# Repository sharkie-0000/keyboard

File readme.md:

# Custom Mechanical Keyboard

My first go at designing and building a custom mechanical keyboard!

This is a custom 60% mechanical keyboard built around a PCB designed in KiCad. This keyboard contains 61 mechanical switches, a Raspberry Pi Pico microcontroller, rotary encoder and small OLED screen.

The aim of this project was to learn how keyboards work internally. I wanted to design a keyboard from scratch including the electrical circuit, switch matrix, PCB design and layout, firmware and case design.

## What is this?

Custom 60% mechanical keyboard with a 61-key layout and custom PCB

Features a 5 row x 14 column switch matrix with individual diodes on each switch to reduce the chance of accidental keystrokes when multiple keys are pressed.

Includes:
Raspberry Pi Pico (RP2040) main controller
61 mechanical switches
61 matrix diodes
Rotary encoder with push button
0.96 inch OLED screen
Custom PCB and 3D designed case components

## Why build this?

This was my first mechanical keyboard project and I wanted to push myself a bit.

I’ve always had an interest in understanding electronics, therefore building a mechanical keyboard was a great opportunity to get hands on with electronics, PCB design, CAD and programming.

I wanted to learn:
How to create a circuit schematic design.
Learn how keyboards use switch matrices.
Understand microcontrollers and GPIO pins.
Create a custom PCB layout using KiCad.
Build a physical keyboard case and plate.
Program firmware to detect key presses.
Get a full understanding of how a custom electronic product is created.

Overall I wanted to create my own keyboard and learn from any mistakes I would make.

## Inspiration

I was inspired by custom mechanical keyboards and the diy keyboard community.

I really like the idea of creating your own keyboard based on your own preferences.

This lead me into creating a 60% sized keyboard. This means it contains all the main keys but takes up less space.

I also wanted a few extra features included such as a rotary encoder and OLED display to make the keyboard more interesting and give me more to learn.

## Features

61 Key compact keyboard layout.
Custom designed PCB.
Controller is Raspberry Pi Pico / RP2040.
Switch matrix 5 rows x 14 columns.
Each switch has its own diode.
Rotary encoder with push button.
0.96" OLED screen.
Custom 3D designed case / plate files.
Firmware was written for Raspberry Pi Pico.

## Repository Structure

```text
.
├── bom.csv
├── cad/
│   ├── pcb.step
│   ├── s-keyboard-plate-1.stl
│   ├── s-keyboard-plate-2.stl
│   └── s-keyboard.f3z
├── firmware/
├── gerber/
├── gerber.zip
├── images/
│   ├── 3d-case-01.png
│   ├── 3d-case-02.png
│   ├── 3d-view-back.png
│   ├── 3d-view-front.png
│   ├── pcb-routing.png
│   └── schamatic.png
├── kicad/
│   ├── s-keyboard.kicad_pcb
│   ├── s-keyboard.kicad_prl
│   ├── s-keyboard.kicad_pro
│   └── s-keyboard.kicad_sch
└── readme.md
```

## Images

### 3D Keyboard and Case Design

### PCB Design

### PCB Routing

### Circuit Schematic

## How it was built

I started my research into keyboard layouts and how mechanical keyboards work.

I decided to go for a 60% style layout with 61 switches, I then used a keyboard layout tool to lay out my switches.

Once I had decided on my switches I created my schematic in KiCad. I arranged the switches in a matrix with rows, columns and individual diodes.

I chose to use a Raspberry Pi Pico as the RP2040 has enough GPIO pins. A rotary encoder and OLED were also added to the circuit.

After my schematic was complete I created my PCB. I added my switches, diodes, controller, OLED and encoder. I then started routing.

CAD files have been included for the PCB and keyboard components.

## PCB Design

The PCB is designed using **KiCad**.

I first created my schematic and organised the switches in to a 5 by 14 grid. There are 61 switches and so there are less switches on the last row.

The switches have been connected using diodes and I have used global labels to show where they go in terms of their row and column.

Once I had completed this I then added the footprints and began designing my PCB.

The PCB contains
    61 switches
    61 diodes
    Connections for Raspberry Pi Pico
    Connections for OLED display
    Connections for rotary encoder

I placed the components on the board and started to route. The KiCad files can be found in the repository along with the Gerber files for manufacturing.

## Components

| Component | Purpose |
|---|---|
| Raspberry Pi Pico (RP2040) | Main microcontroller |
| Mechanical switches | Detect key presses |
| 1N4148 diodes | Keyboard switch matrix |
| Rotary encoder | Additional rotary input |
| 0.96-inch SSD1306 OLED | Small display |
| Custom PCB | Connects all the electronics |
| Keyboard plate and case | Physical keyboard structure |

## Firmware

The firmware will be running on the Raspberry Pi Pico with the RP2040.

The firmware will be responsible for scanning the keyboard matrix and detecting key presses and releases.
The firmware should:
    Configure the GPIO pins for the keyboard matrix.
    Scan all 5 rows and 14 columns.
    Detect key presses and releases.
    Map the matrix to the appropriate keyboard keycodes.
    Handle the rotary encoder and its push button.
    Communicate with the OLED display.

The `firmware/` folder is reserved for the keyboard firmware and related code.

## Keyboard Matrix

The keyboard uses a matrix system.

There are 5 rows and 14 columns in the matrix, meaning there are 70 total positions in the matrix. However, there are only 61 switches on the keyboard.

Each switch has its own diode. The microcontroller scans through the matrix to determine which switches are pressed.

This means that a reduced number of GPIO pins can be used to read all of the keys.

## Assembly Instructions

These are the planned assembly steps once the PCB and physical parts are ready.

**Step 1: Create the PCB**

Use the gerber files inside the gerber/ folder to order your PCB. Inspect the PCB for any damage and ensure the pads and holes are correct.

**Step 2: Gather Components**

Use the BOM to gather all the components, Raspberry Pi Pico, switches, diodes, rotary encoder, OLED and others.

**Step 3: Fit Diodes**

Place the 61 diodes on the PCB. Ensure polarities are correct.

**Step 4: Fit Controller and Electronics**

Place the Raspberry Pi Pico connections, rotary encoder and OLED onto the PCB. Ensure orientation and connections are correct.

**Step 5: Fit Switches**

Place the mechanical switches onto the PCB. Ensure pins are straight.

**Step 6: Create Case**

Use the CAD files inside the cad/ folder to create the case and plate. Assemble the PCB with the keyboard case.

**Step 7: Fit Keycaps**

Place the keycaps according to the intended 61 key layout.

**Step 8: Upload Firmware and Test**

Upload the firmware onto the Raspberry Pi Pico. Test the keys, rotary encoder and OLED.

## Bill of Materials (BOM)

| Component | Quantity | Price | Link |
|---|---:|---:|---|
| Kailh Super Speed Silver MX SMD switches | 70 (61 needed) | ₹4,728.00 | [Buy](https://www.desertcart.in/products/407165603-70-pcs-kailh-super-speed-silver-mx-smd-3-pin) |
| 1N4148 DO-35 switching diodes | 100 (61 needed) | ₹267.00 | [Buy](https://www.amazon.in/Circuit-Ranger-Switching-Electronic-Projects/dp/B0FJLP12GX) |
| EC11 rotary encoder with push switch | 1 | ₹47.25 | [Buy](https://circuitcomps.com/products/ec11-rotary-encoder-20mm-knurled-shaft-with-push-switch) |
| 0.96-inch SSD1306 OLED display | 1 | ₹209.00 | [Buy](https://probots.co.in/0-96-inch-128-x-64-spi-i2c-4pin-oled-blue-display-module-ssd1306-controller.html) |
| PCB Fabrication (JLCPCB) | 1 | $22.00 | [JLCPCB](https://jlcpcb.com/) |
| **Total** | | **₹5,251.25 + $22.00** | |

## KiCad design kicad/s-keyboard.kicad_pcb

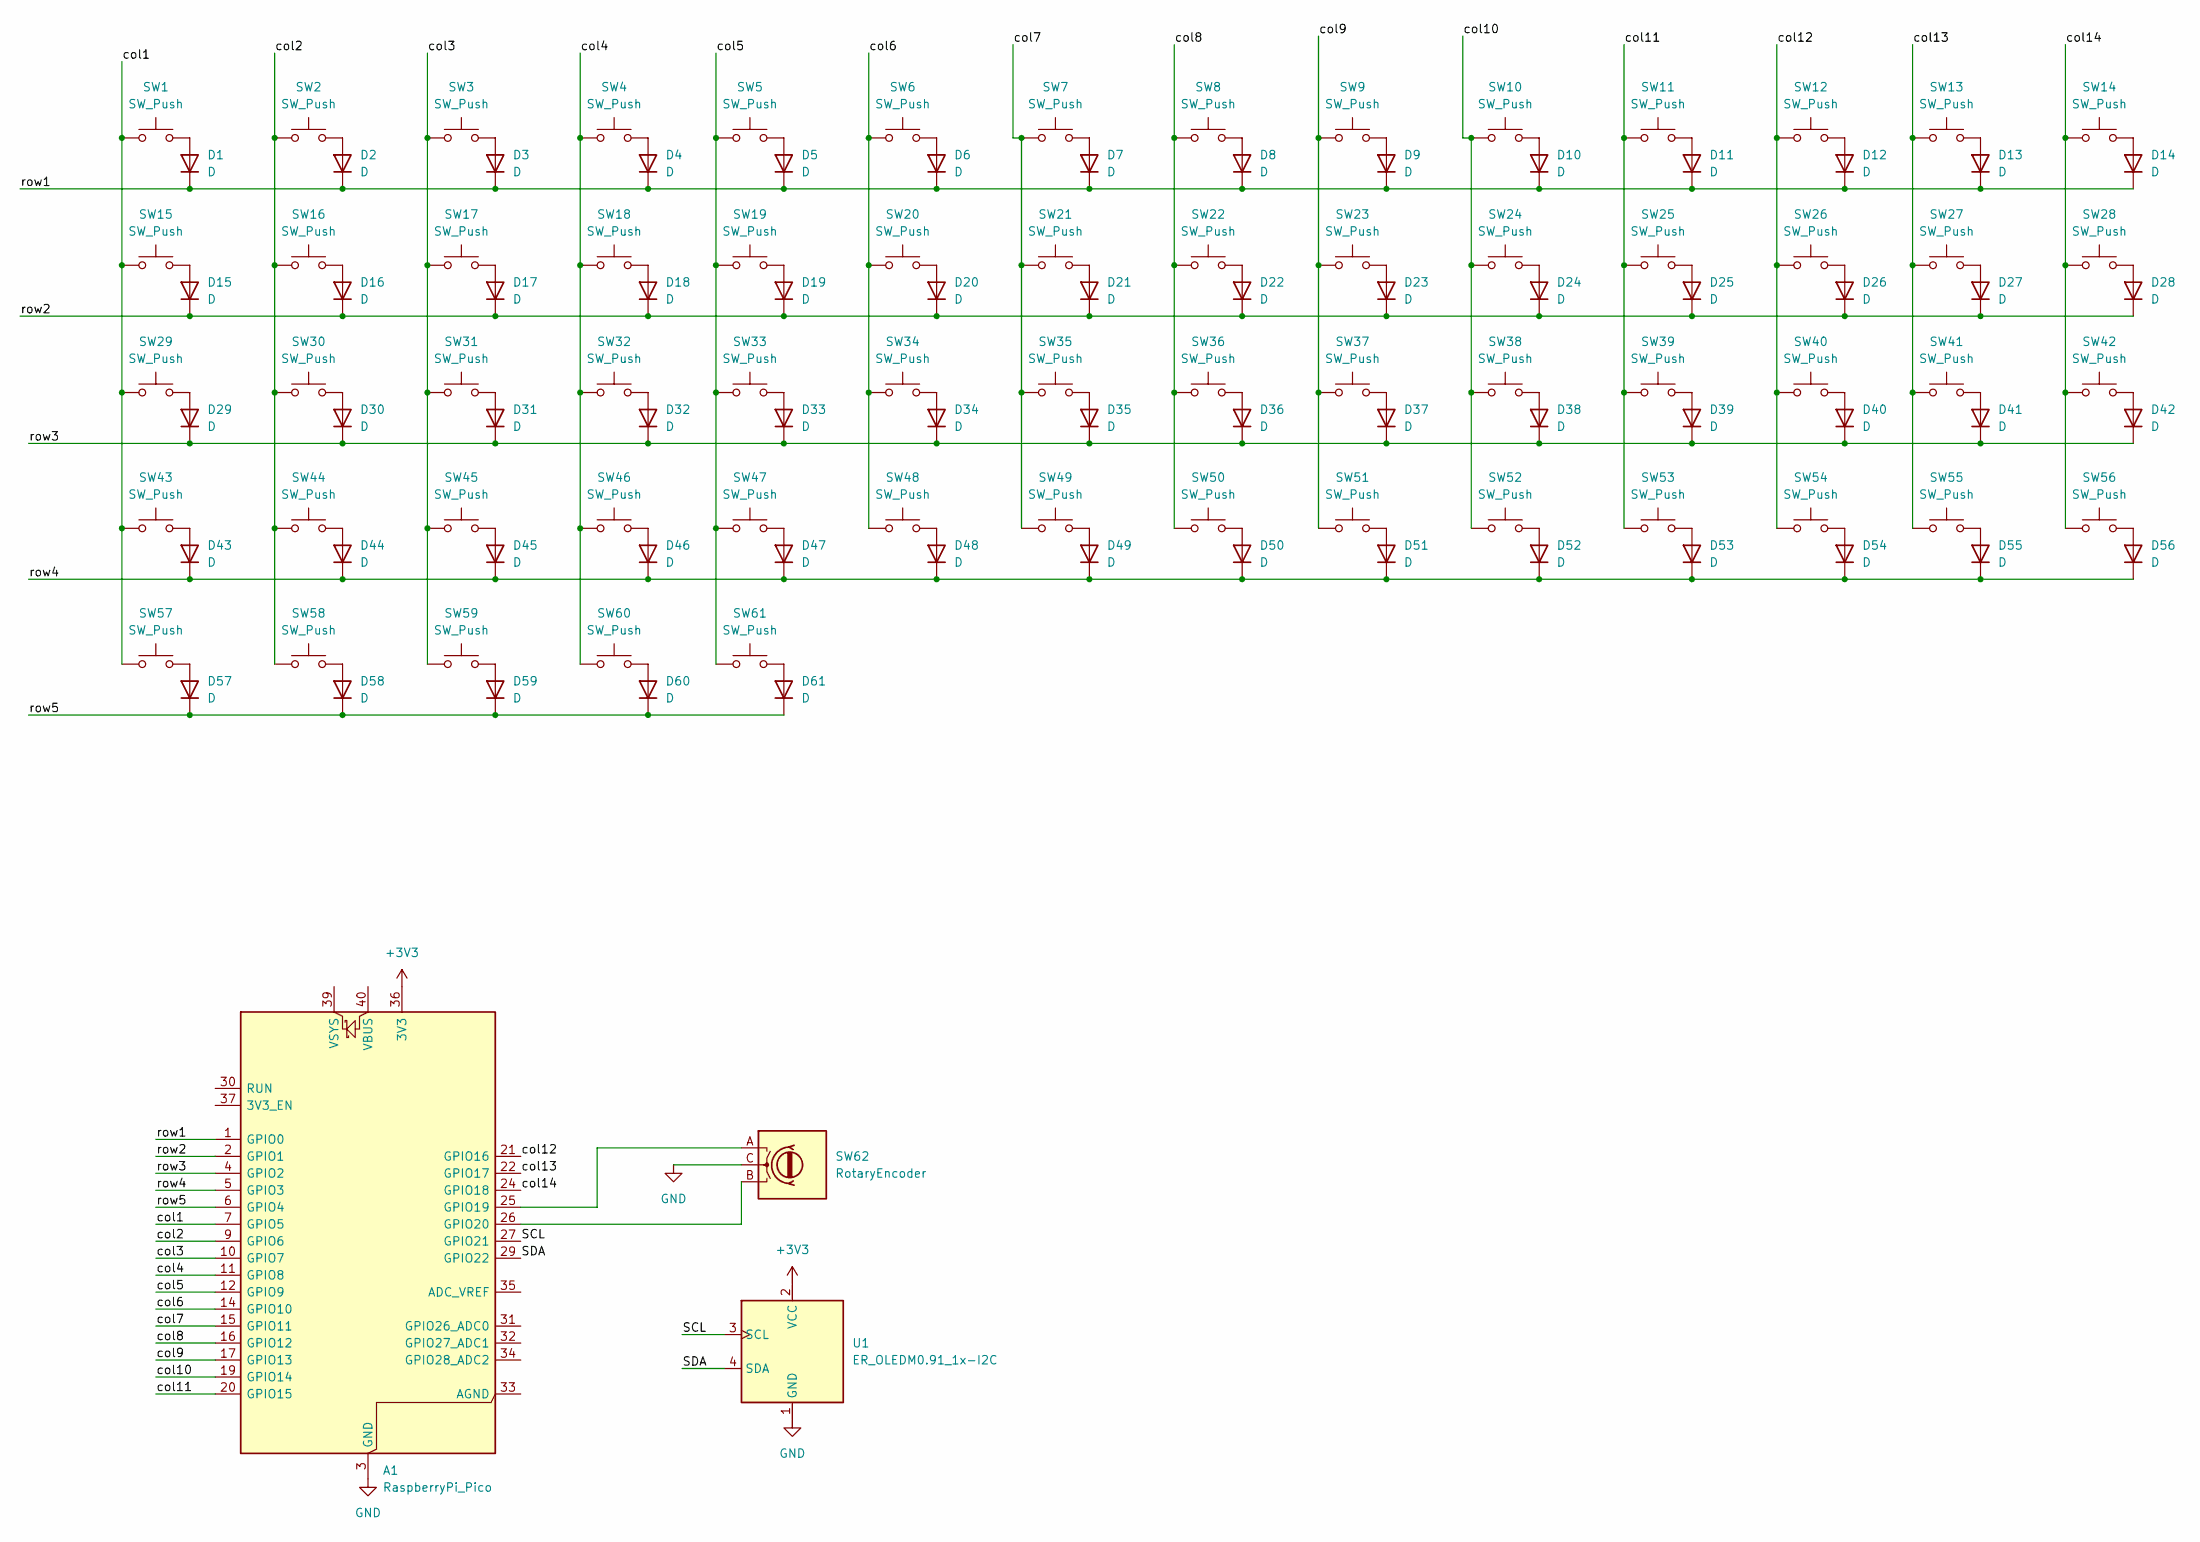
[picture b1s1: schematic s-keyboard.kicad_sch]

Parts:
A1: RaspberryPi_Pico; RaspberryPi_Pico_Common_Unspecified
D1, D2, D3, D4, D5, D6, D7, D8, D9, D10, D11, D12, D13, D14, D15, D16, D17, D18, D19, D20, D21, D22, D23, D24, D25, D26, D27, D28, D29, D30, D31, D32, D33, D34, D35, D36, D37, D38, D39, D40, D41, D42, D43, D44, D45, D46, D47, D48, D49, D50, D51, D52, D53, D54, D55, D56, D57, D58, D59, D60, D61: D; D_SOD-123
SW1, SW2, SW3, SW4, SW5, SW6, SW7, SW8, SW9, SW10, SW11, SW12, SW13, SW14, SW15, SW16, SW17, SW18, SW19, SW20, SW21, SW22, SW23, SW24, SW25, SW26, SW27, SW28, SW29, SW30, SW31, SW32, SW33, SW34, SW35, SW36, SW37, SW38, SW39, SW40, SW41, SW42, SW43, SW44, SW45, SW46, SW47, SW48, SW49, SW50, SW51, SW52, SW53, SW54, SW55, SW56, SW57, SW58, SW59, SW60, SW61: SW_Push; SW_Cherry_MX_1.00u_PCB
SW62: RotaryEncoder; RotaryEncoder_Alps_EC11E_Vertical_H20mm
U1: ER_OLEDM0.91_1x-I2C

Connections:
+3V3: A1.36 (3V3), U1.2 (VCC)
/SCL: A1.27 (GPIO21), U1.3 (SCL)
/SDA: A1.29 (GPIO22), U1.4 (SDA)
/col1: A1.7 (GPIO5), SW1.1, SW15.1, SW29.1, SW43.1, SW57.1
/col2: A1.9 (GPIO6), SW2.1, SW16.1, SW30.1, SW44.1, SW58.1
/col3: A1.10 (GPIO7), SW3.1, SW17.1, SW31.1, SW45.1, SW59.1
/col4: A1.11 (GPIO8), SW4.1, SW18.1, SW32.1, SW46.1, SW60.1
/col5: A1.12 (GPIO9), SW5.1, SW19.1, SW33.1, SW47.1, SW61.1
/col6: A1.14 (GPIO10), SW6.1, SW20.1, SW34.1, SW48.1
/col7: A1.15 (GPIO11), SW7.1, SW21.1, SW35.1, SW49.1
/col8: A1.16 (GPIO12), SW8.1, SW22.1, SW36.1, SW50.1
/col9: A1.17 (GPIO13), SW9.1, SW23.1, SW37.1, SW51.1
/col10: A1.19 (GPIO14), SW10.1, SW24.1, SW38.1, SW52.1
/col11: A1.20 (GPIO15), SW11.1, SW25.1, SW39.1, SW53.1
/col12: A1.21 (GPIO16), SW12.1, SW26.1, SW40.1, SW54.1
/col13: A1.22 (GPIO17), SW13.1, SW27.1, SW41.1, SW55.1
/col14: A1.24 (GPIO18), SW14.1, SW28.1, SW42.1, SW56.1
/row1: A1.1 (GPIO0), D1.1 (K), D2.1 (K), D3.1 (K), D4.1 (K), D5.1 (K), D6.1 (K), D7.1 (K), D8.1 (K), D9.1 (K), D10.1 (K), D11.1 (K), D12.1 (K), D13.1 (K), D14.1 (K)
/row2: A1.2 (GPIO1), D15.1 (K), D16.1 (K), D17.1 (K), D18.1 (K), D19.1 (K), D20.1 (K), D21.1 (K), D22.1 (K), D23.1 (K), D24.1 (K), D25.1 (K), D26.1 (K), D27.1 (K), D28.1 (K)
/row3: A1.4 (GPIO2), D29.1 (K), D30.1 (K), D31.1 (K), D32.1 (K), D33.1 (K), D34.1 (K), D35.1 (K), D36.1 (K), D37.1 (K), D38.1 (K), D39.1 (K), D40.1 (K), D41.1 (K), D42.1 (K)
/row4: A1.5 (GPIO3), D43.1 (K), D44.1 (K), D45.1 (K), D46.1 (K), D47.1 (K), D48.1 (K), D49.1 (K), D50.1 (K), D51.1 (K), D52.1 (K), D53.1 (K), D54.1 (K), D55.1 (K), D56.1 (K)
/row5: A1.6 (GPIO4), D57.1 (K), D58.1 (K), D59.1 (K), D60.1 (K), D61.1 (K)
GND: A1.3 (GND), A1.8 (GND), A1.13 (GND), A1.18 (GND), A1.23 (GND), A1.28 (GND), A1.38 (GND), SW62.C, U1.1 (GND)
unnamed: A1.25 (GPIO19), SW62.A
unnamed: A1.26 (GPIO20), SW62.B
unnamed: D1.2 (A), SW1.2
unnamed: D2.2 (A), SW2.2
unnamed: D3.2 (A), SW3.2
unnamed: D4.2 (A), SW4.2
unnamed: D5.2 (A), SW5.2
unnamed: D6.2 (A), SW6.2
unnamed: D7.2 (A), SW7.2
unnamed: D8.2 (A), SW8.2
unnamed: D9.2 (A), SW9.2
unnamed: D10.2 (A), SW10.2
unnamed: D11.2 (A), SW11.2
unnamed: D12.2 (A), SW12.2
unnamed: D13.2 (A), SW13.2
unnamed: D14.2 (A), SW14.2
unnamed: D15.2 (A), SW15.2
unnamed: D16.2 (A), SW16.2
unnamed: D17.2 (A), SW17.2
unnamed: D18.2 (A), SW18.2
unnamed: D19.2 (A), SW19.2
unnamed: D20.2 (A), SW20.2
unnamed: D21.2 (A), SW21.2
unnamed: D22.2 (A), SW22.2
unnamed: D23.2 (A), SW23.2
unnamed: D24.2 (A), SW24.2
unnamed: D25.2 (A), SW25.2
unnamed: D26.2 (A), SW26.2
unnamed: D27.2 (A), SW27.2
unnamed: D28.2 (A), SW28.2
unnamed: D29.2 (A), SW29.2
unnamed: D30.2 (A), SW30.2
unnamed: D31.2 (A), SW31.2
unnamed: D32.2 (A), SW32.2
unnamed: D33.2 (A), SW33.2
unnamed: D34.2 (A), SW34.2
unnamed: D35.2 (A), SW35.2
unnamed: D36.2 (A), SW36.2
unnamed: D37.2 (A), SW37.2
unnamed: D38.2 (A), SW38.2
unnamed: D39.2 (A), SW39.2
unnamed: D40.2 (A), SW40.2
unnamed: D41.2 (A), SW41.2
unnamed: D42.2 (A), SW42.2
unnamed: D43.2 (A), SW43.2
unnamed: D44.2 (A), SW44.2
unnamed: D45.2 (A), SW45.2
unnamed: D46.2 (A), SW46.2
unnamed: D47.2 (A), SW47.2
unnamed: D48.2 (A), SW48.2
unnamed: D49.2 (A), SW49.2
unnamed: D50.2 (A), SW50.2
unnamed: D51.2 (A), SW51.2
unnamed: D52.2 (A), SW52.2
unnamed: D53.2 (A), SW53.2
unnamed: D54.2 (A), SW54.2
unnamed: D55.2 (A), SW55.2
unnamed: D56.2 (A), SW56.2
unnamed: D57.2 (A), SW57.2
unnamed: D58.2 (A), SW58.2
unnamed: D59.2 (A), SW59.2
unnamed: D60.2 (A), SW60.2
unnamed: D61.2 (A), SW61.2

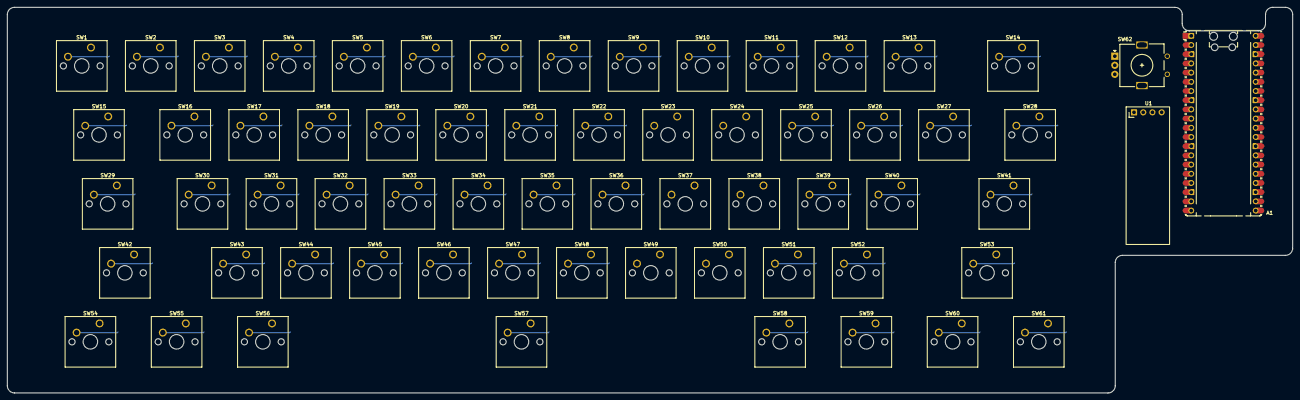
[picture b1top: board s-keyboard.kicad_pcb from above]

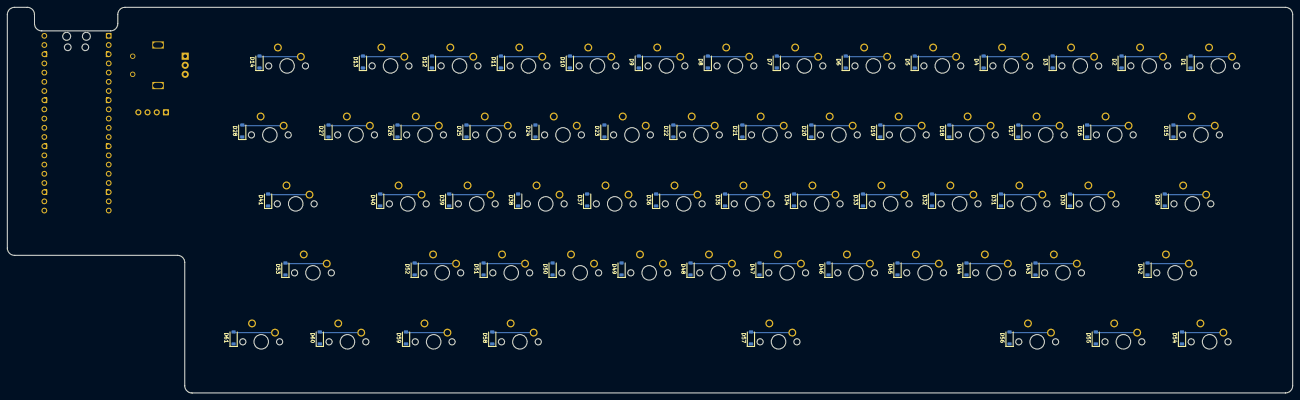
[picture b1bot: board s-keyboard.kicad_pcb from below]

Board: 2 copper layers, 355.0 x 106.5 mm, 125 parts (61 on the bottom side), 86 nets.
